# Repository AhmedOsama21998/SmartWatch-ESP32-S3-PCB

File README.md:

# Smartwatch PCB — ESP32-S3

A work-in-progress smartwatch PCB designed in KiCad around an ESP32-S3-WROOM-1 module. The current schematic includes USB-C power input, Li-ion battery charging and protection, 3.3 V regulation, a push-button/power-latch circuit, and the ESP32-S3 module.

> **Status: Work in progress.** The NTC temperature sensor and MAX30102 breakout module have not yet been added to the schematic/PCB. This revision is not a completed smartwatch design and has not been represented as fabricated or functionally tested.

## Current Design Highlights

- **MCU:** ESP32-S3-WROOM-1
- **USB-C input:** USB 2.0 receptacle used for power input in the current schematic; CC pull-down resistors are shown.
- **Battery charging:** TP4056-based single-cell Li-ion charging circuit.
- **Battery protection:** DW01A with FS8205A dual MOSFET.
- **3.3 V rail:** AP2112K-3.3 regulator.
- **Power control:** Push button and discrete power-latch circuitry.
- **PCB form factor:** Circular board with a marked antenna keep-out region.

The list above describes what is visible in the current KiCad source files. Confirm component ratings, power-path behavior, charging current, thermal limits, antenna clearances, and battery safety before fabrication.

## Planned Additions

- [ ] Add an NTC temperature-sensing circuit and connector/footprint as required.
- [ ] Integrate a ready-made MAX30102 breakout module for heart-rate and SpO₂ sensing, including power, GND, SDA, and SCL connections; verify the module's supply voltage and logic-level compatibility.
- [ ] Check ESP32-S3 GPIO assignments and I²C pull-up strategy.
- [ ] Re-route the PCB after the new components are placed.
- [ ] Run ERC and DRC on the revised design.
- [ ] Review the antenna keep-out and RF layout against the module manufacturer's guidance.
- [ ] Generate and inspect final Gerber/drill outputs after design freeze.
- [ ] Fabricate and test the board before claiming functional validation.

## Design Images

### Current PCB — front / component side

### Current PCB — back side

### Current schematic

## Repository Structure

```text
.
├── KiCad/
│   ├── SmartWatch.kicad_pro
│   ├── SmartWatch.kicad_sch
│   └── SmartWatch.kicad_pcb
├── Images/
│   ├── smartwatch-pcb-front-3d-layout.png
│   ├── smartwatch-pcb-back-3d-layout.png
│   └── smartwatch-schematic-current-revision.png
├── Documentation/
└── README.md
```

## Opening the Project

1. Download or clone this repository.
2. Open `KiCad/SmartWatch.kicad_pro` in KiCad 9.
3. Review the schematic and PCB together.
4. Complete the planned additions before generating manufacturing files.
5. Run ERC and DRC after each substantial revision.

## Validation Status

- [x] Current KiCad project files included
- [x] Current design screenshots included
- [ ] NTC added
- [ ] MAX30102 added
- [ ] ERC/DRC reviewed on the final revision
- [ ] Final Gerbers generated and inspected
- [ ] PCB fabricated
- [ ] Hardware assembled and functionally tested

## License

No open-source license is included in this work-in-progress package yet. Choose and add a license before publishing the design for reuse.

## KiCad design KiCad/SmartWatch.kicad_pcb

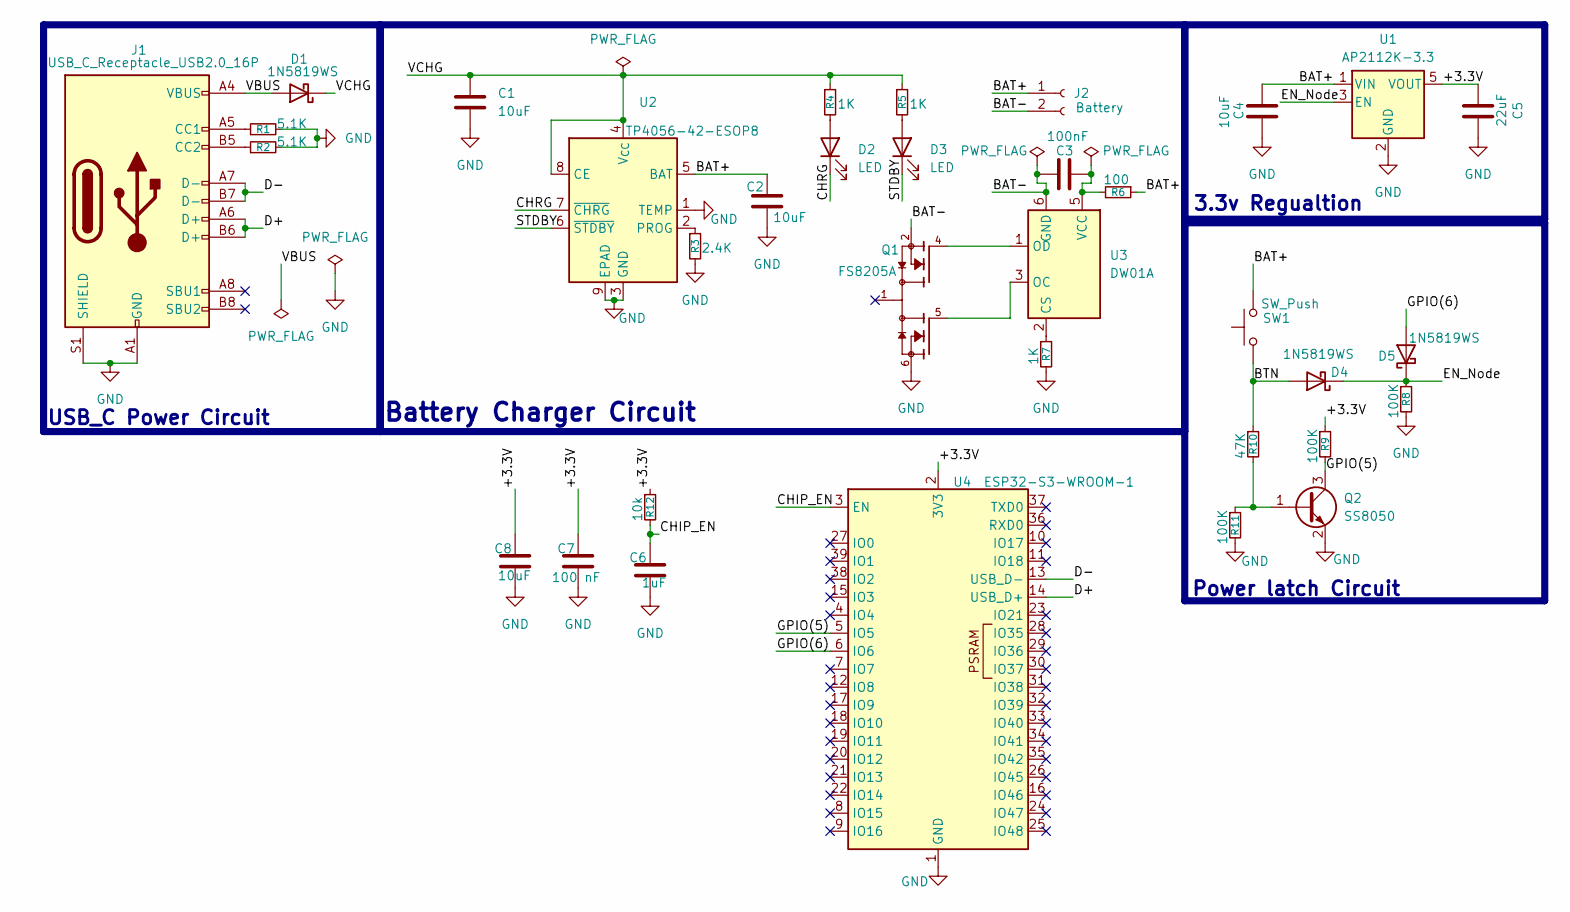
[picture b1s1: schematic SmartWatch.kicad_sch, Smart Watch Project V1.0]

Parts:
C1, C2, C4, C8: 10uF; C_0805_2012Metric
C3: 100nF; C_0805_2012Metric
C5: 22uF; C_0805_2012Metric
C6: 1uF; C_0805_2012Metric
C7: 100 nF; C_0805_2012Metric
D1, D4, D5: 1N5819WS; D_SOD-123
D2, D3: LED; LED_1206_3216Metric_Pad1.42x1.75mm_HandSolder
J1: USB_C_Receptacle_USB2.0_16P; USB_C_Receptacle_GCT_USB4105-xx-A_16P_TopMnt_Horizontal
J2: Battery; JST_PH_S2B-PH-K_1x02_P2.00mm_Horizontal
Q1: FS8205A; SOP65P640X120-8N; PARTREV 1.7
Q2: SS8050; SOT-23
R1, R2: 5.1K; R_0805_2012Metric
R3: 2.4K; R_0805_2012Metric
R4, R5, R7: 1K; R_0805_2012Metric
R6: 100; R_0805_2012Metric
R8, R9, R11: 100K; R_0805_2012Metric
R10: 47K; R_0805_2012Metric
R12: 10k; R_0805_2012Metric
SW1: SW_Push; SW_Tactile_SPST_NO_Straight_CK_PTS636Sx25SMTRLFS
U1: AP2112K-3.3; SOT-23-5
U2: TP4056-42-ESOP8; SOIC-8-1EP_3.9x4.9mm_P1.27mm_EP2.41x3.3mm
U3: DW01A; SOT-23-6
U4: ESP32-S3-WROOM-1

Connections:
/+3.3V: C5.1, C7.1, C8.1, R9.1, R12.1, U1.5 (VOUT), U4.2 (3V3)
/BAT+: C2.1, C4.1, J2.1, R6.1, SW1.2, U1.1 (VIN), U2.5 (BAT)
/BAT-: C3.2, J2.2, Q1.2, Q1.3, U3.6 (GND)
/BTN: D4.2 (A), R10.1, SW1.1
/CHIP_EN: C6.1, R12.2, U4.3 (EN)
/CHRG: D2.1 (K), U2.7 (~CHRG)
/D+: J1.A6 (D+), J1.B6 (D+), U4.14 (USB_D+)
/D-: J1.A7 (D-), J1.B7 (D-), U4.13 (USB_D-)
/EN_Node: D4.1 (K), D5.1 (K), R8.1, U1.3 (EN)
/GPIO(5): Q2.3 (C), R9.2, U4.5 (IO5)
/GPIO(6): D5.2 (A), U4.6 (IO6)
/STDBY: D3.1 (K), U2.6 (~STDBY)
/VBUS: D1.2 (A), J1.A4 (VBUS), J1.A9 (VBUS), J1.B4 (VBUS), J1.B9 (VBUS)
/VCHG: C1.1, D1.1 (K), R4.1, R5.1, U2.4 (V_{CC}), U2.8 (CE)
GND: C1.2, C2.2, C4.2, C5.2, C6.2, C7.2, C8.2, J1.A1 (GND), J1.A12 (GND), J1.B1 (GND), J1.B12 (GND), J1.S1 (SHIELD), Q1.6, Q1.7, Q2.2 (E), R1.2, R2.2, R3.2, R7.2, R8.2, R11.2, U1.2 (GND), U2.1 (TEMP), U2.3 (GND), U2.9 (EPAD), U4.1 (GND), U4.40 (GND), U4.41 (GND)
unnamed: D2.2 (A), R4.2
unnamed: D3.2 (A), R5.2
unnamed: J1.A5 (CC1), R1.1
unnamed: J1.B5 (CC2), R2.1
unnamed: Q2.1 (B), R10.2, R11.1
unnamed: R3.1, U2.2 (PROG)
unnamed: R7.1, U3.2 (CS)
unnamed: Q1.5, U3.3 (OC)
unnamed: Q1.4, U3.1 (OD)
unnamed: C3.1, R6.2, U3.5 (VCC)

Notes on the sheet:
Battery Charger Circuit
3.3v Regualtion
Power latch Circuit
USB_C Power Circuit

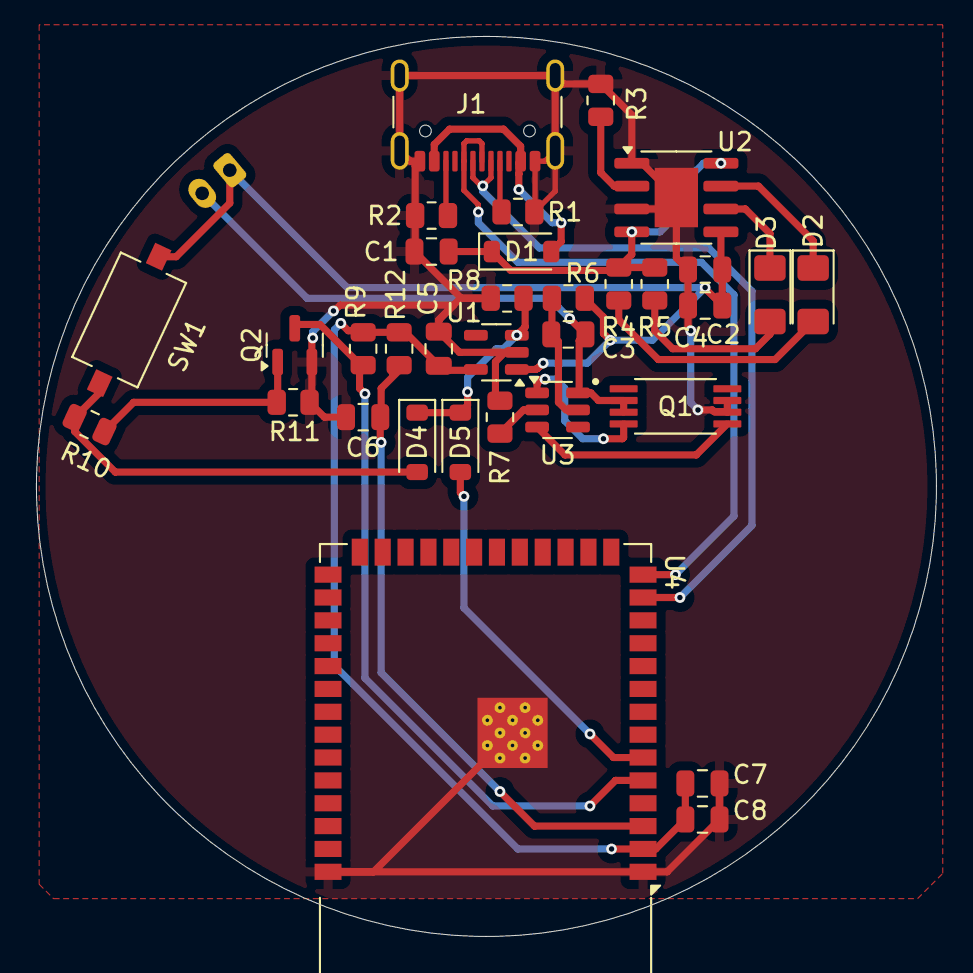
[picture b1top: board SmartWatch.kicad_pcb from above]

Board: 2 copper layers, 50.0 x 50.0 mm, 34 parts (1 on the bottom side), 25 nets.
